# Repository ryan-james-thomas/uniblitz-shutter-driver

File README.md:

# Shutter Driver for uni-stable Uniblitz laser shutters

This shutter driver is designed to work with uni-stable Uniblitz shutters, and it is based on an old shutter driver design from the University of Otago Kjaergaard Lab.  It requires two power rails at +12 V and +60-70 V with a common ground.  When initially powered, up to two 47 uF capacitors are charged from the high-voltage rail, with the charging current being limited by up to four 1 kOhm, 2 W resistors.  On the rising edge of a control signal, this stored energy is switched into the shutter using two PNP transistors in the Darlington configuration which should give a nominal current spike of approximately 1.2 A.  The length of this spike can be varied by a factor of 2 using a trim-pot or, for shorter pulses, a capacitor (C3) can be replaced with a smaller value.  Testing has shown that a 1 nF capacitor and a total of 200 kOhm of resistance between R8 and RV1 will open shutters in good condition.  When the inital voltage/current spike has decayed a 200 mA holding current is provided to keep the shutter open.  To close the shutter the holding current is switched off using another PNP transistor.  To reduce voltage transients and ensure a fast closing time, a reverse-biased diode and a 1.8 kOhm resistor are connected to the shutter net, and these act to increase the rate at which the inductively generated negative voltage transient decays.  

The control signal is generated from an isolated 3 - 5 V digital input.  The relative polarity between the control signal and the input can be changed using a SPST switch.

Each board will draw up to 300 mA of current at +12 V and 60 mA of current at +60 V for each current-limiting resistor (R5, R14-R16).  Most applications will only need one current-limiting resistor and one storage capacitor.  More of these allow for faster charging, more charge storage, and therefore shorter delays between 'on' events.

Lists of parts can be found in the files 'Shutter_Driver.txt' and 'Auxiliary Parts.txt'.

Project files created with KiCAD 5.1.4.

## Enclosure
A diagram for the drilling out mounting holes for an enclosure containing 5 boards can be found in the file enclosure.pdf

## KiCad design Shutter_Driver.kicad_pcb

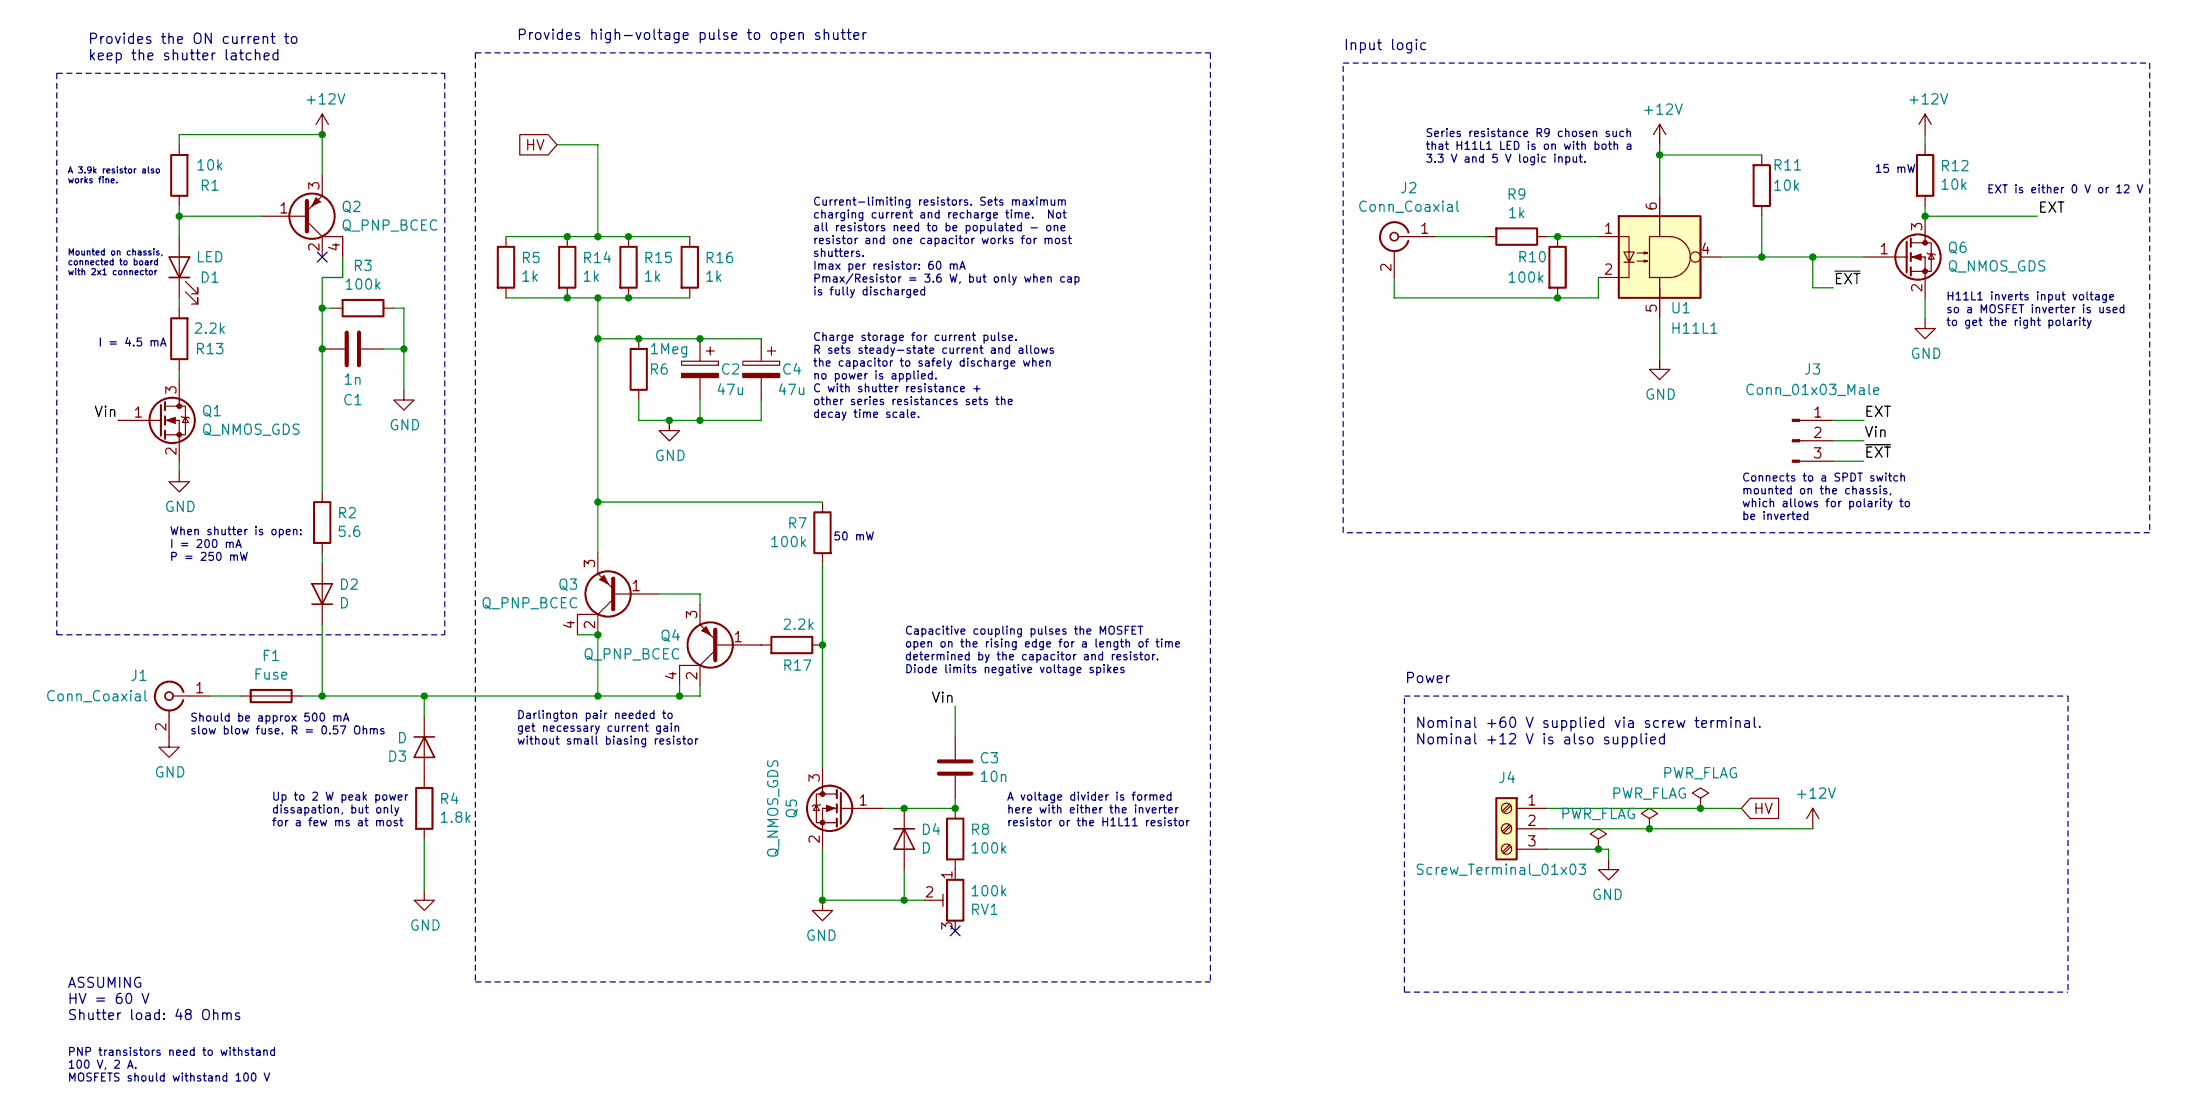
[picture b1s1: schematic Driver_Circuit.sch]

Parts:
C1: 1n; C_1206_3216Metric_Pad1.42x1.75mm_HandSolder; Digikey Part Number 732-8115-1-ND
C2, C4: 47u; CP_Radial_D10.0mm_P5.00mm; Digikey Part Number 399-15665-ND
C3: 10n; C_1206_3216Metric_Pad1.42x1.75mm_HandSolder; Digikey Part Number 1276-1035-1-ND
D1: LED; PinHeader_1x02_P2.54mm_Vertical; Digikey Part Number C5SMF-RJF-CT0W0BB1-ND
D2, D3, D4: D; D_5W_P10.16mm_Horizontal; Digikey Part Number 1N4005-TPMSCT-ND
F1: Fuse; Fuseholder_Wurth_15mm; Digikey Part Number 732-11374-ND
J1, J2: Conn_Coaxial; BNC_Amphenol_B6252HB-NPP3G-50_Horizontal; Digikey Part Number WM5514-ND
J3: Conn_01x03_Male; PinHeader_1x03_P2.54mm_Vertical; Digikey Part Number 2057-PH1-03-UA-ND
J4: Screw_Terminal_01x03; TerminalBlock_bornier-3_P5.08mm; Digikey Part Number 732-10956-ND
Q1, Q5, Q6: Q_NMOS_GDS; SOT-23_Handsoldering; Digikey Part Number BSS123-FDICT-ND
Q2, Q3, Q4: Q_PNP_BCEC; SOT-223; Digikey Part Number CZT955CT-ND
R1, R11, R12: 10k; R_1206_3216Metric_Pad1.42x1.75mm_HandSolder; Digikey Part Number RMCF1206JT10K0CT-ND
R2: 5.6; R_Axial_DIN0207_L6.3mm_D2.5mm_P10.16mm_Horizontal; Digikey Part Number S5.6HCT-ND
R3, R7, R8, R10: 100k; R_1206_3216Metric_Pad1.42x1.75mm_HandSolder; Digikey Part Number RMCF1206JT100KCT-ND
R4: 1.8k; R_Axial_DIN0207_L6.3mm_D2.5mm_P10.16mm_Horizontal; Digikey Part Number CF12JT1K80CT-ND
R5, R14, R15, R16: 1k; R_Axial_DIN0414_L11.9mm_D4.5mm_P15.24mm_Horizontal; Digikey Part Number RSMF2JT1K00CT-ND
R6: 1Meg; R_1206_3216Metric_Pad1.42x1.75mm_HandSolder; Digikey Part Number RMCF1206JG1M00CT-ND
R9: 1k; R_1206_3216Metric_Pad1.42x1.75mm_HandSolder; Digikey Part Number RMCF1206JT1K00CT-ND
R13, R17: 2.2k; R_1206_3216Metric_Pad1.42x1.75mm_HandSolder; Digikey Part Number RMCF1206JT2K20CT-ND
RV1: 100k; Potentiometer_Bourns_3296X_Horizontal; Digikey Part Number 490-2895-ND
U1: H11L1; SMDIP-6_W9.53mm; Digikey Part Number 1080-1201-1-ND

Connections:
+12V: J4.2, Q2.3 (E), R1.2, R11.2, R12.1, U1.6
/Driver_Circuit/EXT: J3.1, Q6.3 (D), R12.2
/Driver_Circuit/Vin: C3.2, J3.2, Q1.1 (G)
/Driver_Circuit/~EXT: J3.3, Q6.1 (G), R11.1, U1.4
GND: C1.2, C2.2, C4.2, D4.2 (A), J1.2 (Ext), J4.3, Q1.2 (S), Q5.2 (S), Q6.2 (S), R3.1, R4.2, R6.1, RV1.2, U1.5
HV: J4.1, R5.1, R14.1, R15.1, R16.1
unnamed: C1.1, Q2.4 (C), R2.1, R3.2
unnamed: C2.1, C4.1, Q3.3 (E), R5.2, R6.2, R7.1, R14.2, R15.2, R16.2
unnamed: C3.1, D4.1 (K), Q5.1 (G), R8.1
unnamed: D1.1 (K), R13.2
unnamed: D1.2 (A), Q2.1 (B), R1.1
unnamed: D2.1 (K), D3.1 (K), F1.1, Q3.2 (C), Q3.4 (C), Q4.2 (C), Q4.4 (C)
unnamed: D2.2 (A), R2.2
unnamed: D3.2 (A), R4.1
unnamed: F1.2, J1.1 (In)
unnamed: J2.1 (In), R9.2
unnamed: J2.2 (Ext), R10.2, U1.2
unnamed: Q1.3 (D), R13.1
unnamed: Q3.1 (B), Q4.3 (E)
unnamed: Q4.1 (B), R17.2
unnamed: Q5.3 (D), R7.2, R17.1
unnamed: R8.2, RV1.1
unnamed: R9.1, R10.1, U1.1

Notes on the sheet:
Series resistance R9 chosen such that H11L1 LED is on with both a 3.3 V and 5 V logic input.
H11L1 inverts input voltage so a MOSFET inverter is used to get the right polarity
Provides the ON current to keep the shutter latched
EXT is either 0 V or 12 V
Charge storage for current pulse. R sets steady-state current and allows the capacitor to safely discharge when no power is applied. C with shutter resistance + other series resistances sets the decay time scale.
When shutter is open: I = 200 mA P = 250 mW
ASSUMING HV = 60 V Shutter load: 48 Ohms
Darlington pair needed to get necessary current gain without small biasing resistor
50 mW
15 mW
Provides high-voltage pulse to open shutter
PNP transistors need to withstand 100 V, 2 A. MOSFETS should withstand 100 V
Connects to a SPDT switch mounted on the chassis, which allows for polarity to be inverted
Current-limiting resistors. Sets maximum charging current and recharge time. Not all resistors need to be populated - one resistor and one capacitor works for most shutters. Imax per resistor: 60 mA Pmax/Resistor = 3.6 W, but only when cap is fully discharged
Capacitive coupling pulses the MOSFET open on the rising edge for a length of time determined by the capacitor and resistor. Diode limits negative voltage spikes
A voltage divider is formed here with either the inverter resistor or the H1L11 resistor
Up to 2 W peak power dissapation, but only for a few ms at most
Nominal +60 V supplied via screw terminal. Nominal +12 V is also supplied
Power
Input logic
Mounted on chassis, connected to board with 2x1 connector
Should be approx 500 mA slow blow fuse. R = 0.57 Ohms
I = 4.5 mA
A 3.9k resistor also works fine.

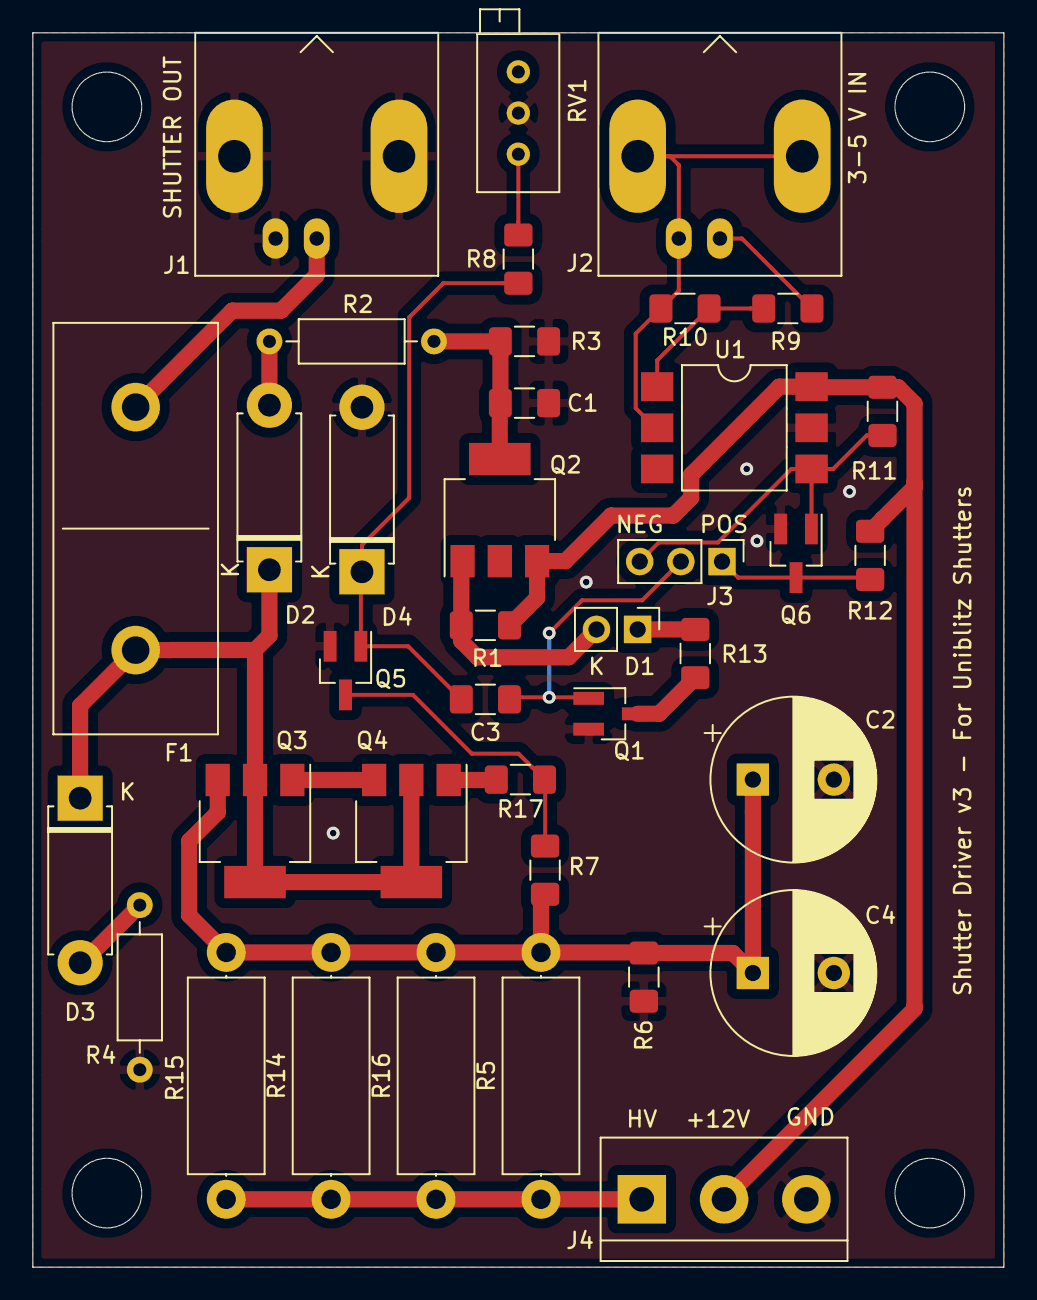
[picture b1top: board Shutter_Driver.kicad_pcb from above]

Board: 2 copper layers, 59.9 x 76.2 mm, 38 parts (0 on the bottom side), 23 nets.

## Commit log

2023-01-15 Initial commit for finished project.
    Project files created with KiCAD 5.1.4.
